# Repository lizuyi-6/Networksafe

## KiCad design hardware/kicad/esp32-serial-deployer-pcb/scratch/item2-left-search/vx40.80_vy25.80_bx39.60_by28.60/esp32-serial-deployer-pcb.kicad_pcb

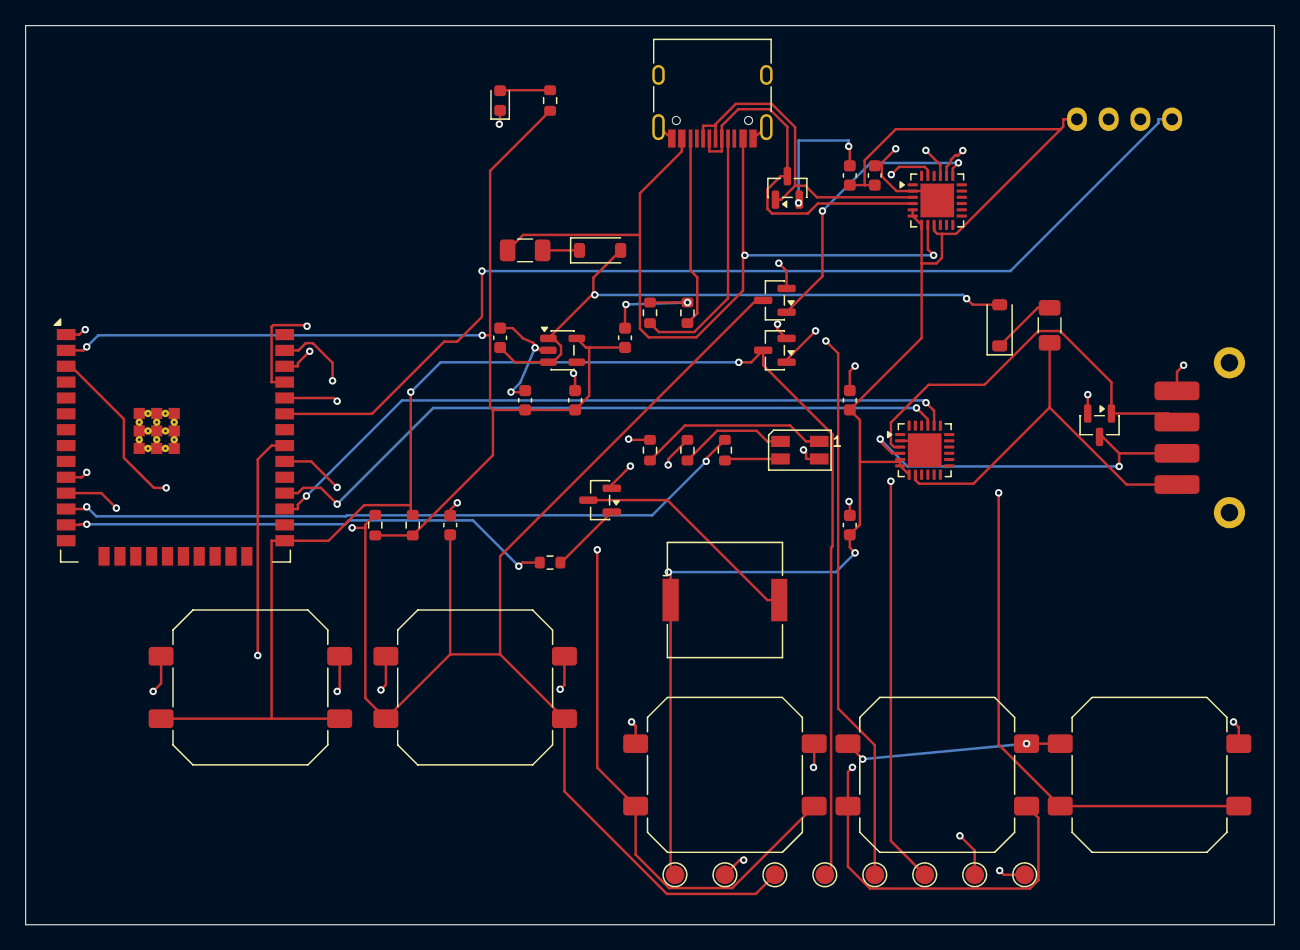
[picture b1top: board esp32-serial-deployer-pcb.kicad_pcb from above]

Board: 4 copper layers, 100.0 x 72.0 mm, 50 parts (0 on the bottom side), 36 nets.

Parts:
BZ1: Buzzer; Buzzer_Murata_PKMCS0909E
C1, C2, C9: 10u; C_0603_1608Metric
C3: 1u; C_0603_1608Metric
C4, C6, C8: 0.1u; C_0603_1608Metric
C5, C7: 4.7u; C_0603_1608Metric
D1, D2: B5819W; D_SOD-123
D3: PWR LED; LED_0603_1608Metric
D10: RGB LED; LED_RGB_Wuerth-PLCC4_3.2x2.8mm_150141M173100
F1, F2: PTC500mA; Fuse_1206_3216Metric
J1: Service USB-C; USB_C_Receptacle_HRO_TYPE-C-31-M-12
J2: USB-A Pigtail; USB_A_Pigtail_Pads_1x4_Edge
J3: OLED 0.96in I2C; OLED_096_I2C_Module_1x4
Q1, Q2, Q3: MMBT3904; SOT-23
R1, R2: 5.1k; R_0603_1608Metric
R3, R4: 10k; R_0603_1608Metric
R13, R14, R15: 330; R_0603_1608Metric
R16: 1k; R_0603_1608Metric
R17: 4.7k; R_0603_1608Metric
SW1: BOOT; SW_Push_1P1T_NO_CK_PTS125Sx43SMTR
SW2: RESET; SW_Push_1P1T_NO_CK_PTS125Sx43SMTR
SW3: OK; SW_Push_1P1T_NO_CK_PTS125Sx43SMTR
SW4: NEXT; SW_Push_1P1T_NO_CK_PTS125Sx43SMTR
SW5: BACK; SW_Push_1P1T_NO_CK_PTS125Sx43SMTR
TP1: 3V3; TestPoint_Pad_D1.5mm
TP2: GND; TestPoint_Pad_D1.5mm
TP3: EN; TestPoint_Pad_D1.5mm
TP4: IO0; TestPoint_Pad_D1.5mm
TP5: TX0; TestPoint_Pad_D1.5mm
TP6: RX0; TestPoint_Pad_D1.5mm
TP7: TX2; TestPoint_Pad_D1.5mm
TP8: RX2; TestPoint_Pad_D1.5mm
U1: ESP32-WROOM-32E
U2: CP2102N Service; QFN-24-1EP_4x4mm_P0.5mm_EP2.7x2.7mm
U3: CP2102N Host; QFN-24-1EP_4x4mm_P0.5mm_EP2.7x2.7mm
U4: AP2112K-3.3; SOT-23-5
U5, U6: USB ESD; SOT-23

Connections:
3V3: BZ1.1, C2.1, C4.1, C5.1, C6.1, C7.1, C8.1, C9.1, J3.1, R3.1, R4.1, R16.1, TP1.1, U1.2, U2.5, U2.6, U2.7, U2.9, U3.5, U3.6, U3.7, U3.9, U4.5
5V_SYS: C1.1, D1.2, D2.2, U4.1, U4.3
BTN_BACK: SW5.1, U1.37
BTN_NEXT: SW4.1, U1.31
BTN_OK: SW3.1, U1.30
BUZZER_CTRL: R17.1, U1.13
BUZZER_CTRL_DRV: Q3.1, R17.2
BUZZER_SW: BZ1.2, Q3.3
ESP_EN: C3.1, Q1.3, R3.2, SW2.1, TP3.1, U1.3
ESP_IO0: Q2.3, R4.2, SW1.1, TP4.1, U1.25
GND: C1.2, C2.2, C3.2, C4.2, C5.2, C6.2, C7.2, C8.2, C9.2, D3.1, D10.2, J1.A1, J1.A12, J1.B1, J1.B12, J1.S1, J2.4, J3.2, Q1.2, Q2.2, Q3.2, R1.2, R2.2, SW1.2, SW2.2, SW3.2, SW4.2, SW5.2, TP2.1, U1.1, U1.39, U2.2, U2.25, U3.2, U3.25, U4.2, U5.2, U6.2
HOST_DN: J2.2, U3.4, U6.3
HOST_DP: J2.3, U3.3, U6.1
LED_B: D10.4, R15.1
LED_B_DRV: R15.2, U1.12
LED_G: D10.3, R14.1
LED_G_DRV: R14.2, U1.11
LED_R: D10.1, R13.1
LED_R_DRV: R13.2, U1.10
OLED_SCL: J3.3, U1.36
OLED_SDA: J3.4, U1.33
PWR_LED_N: D3.2, R16.2
UART0_RX: TP6.1, U1.34, U2.20
UART0_TX: TP5.1, U1.35, U2.21
UART2_RX: TP8.1, U1.27, U3.20
UART2_TX: TP7.1, U1.28, U3.21
USB_CC1: J1.A5, R1.1
USB_CC2: J1.B5, R2.1
USB_C_DN: J1.A7, J1.B7, U2.4, U5.3
USB_C_DP: J1.A6, J1.B6, U2.3, U5.1
USB_DTR: Q2.1, U2.23
USB_RTS: Q1.1, U2.19
VBUS_HOST_PROT: D2.1, F2.2
VBUS_HOST_RAW: F2.1, J2.1, U3.8
VBUS_USB_C_PROT: D1.1, F1.2
VBUS_USB_C_RAW: F1.1, J1.A4, J1.A9, J1.B4, J1.B9, U2.8
